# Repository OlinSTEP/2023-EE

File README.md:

# 2023-EE
Firmware and EE documents for 2023 STEP

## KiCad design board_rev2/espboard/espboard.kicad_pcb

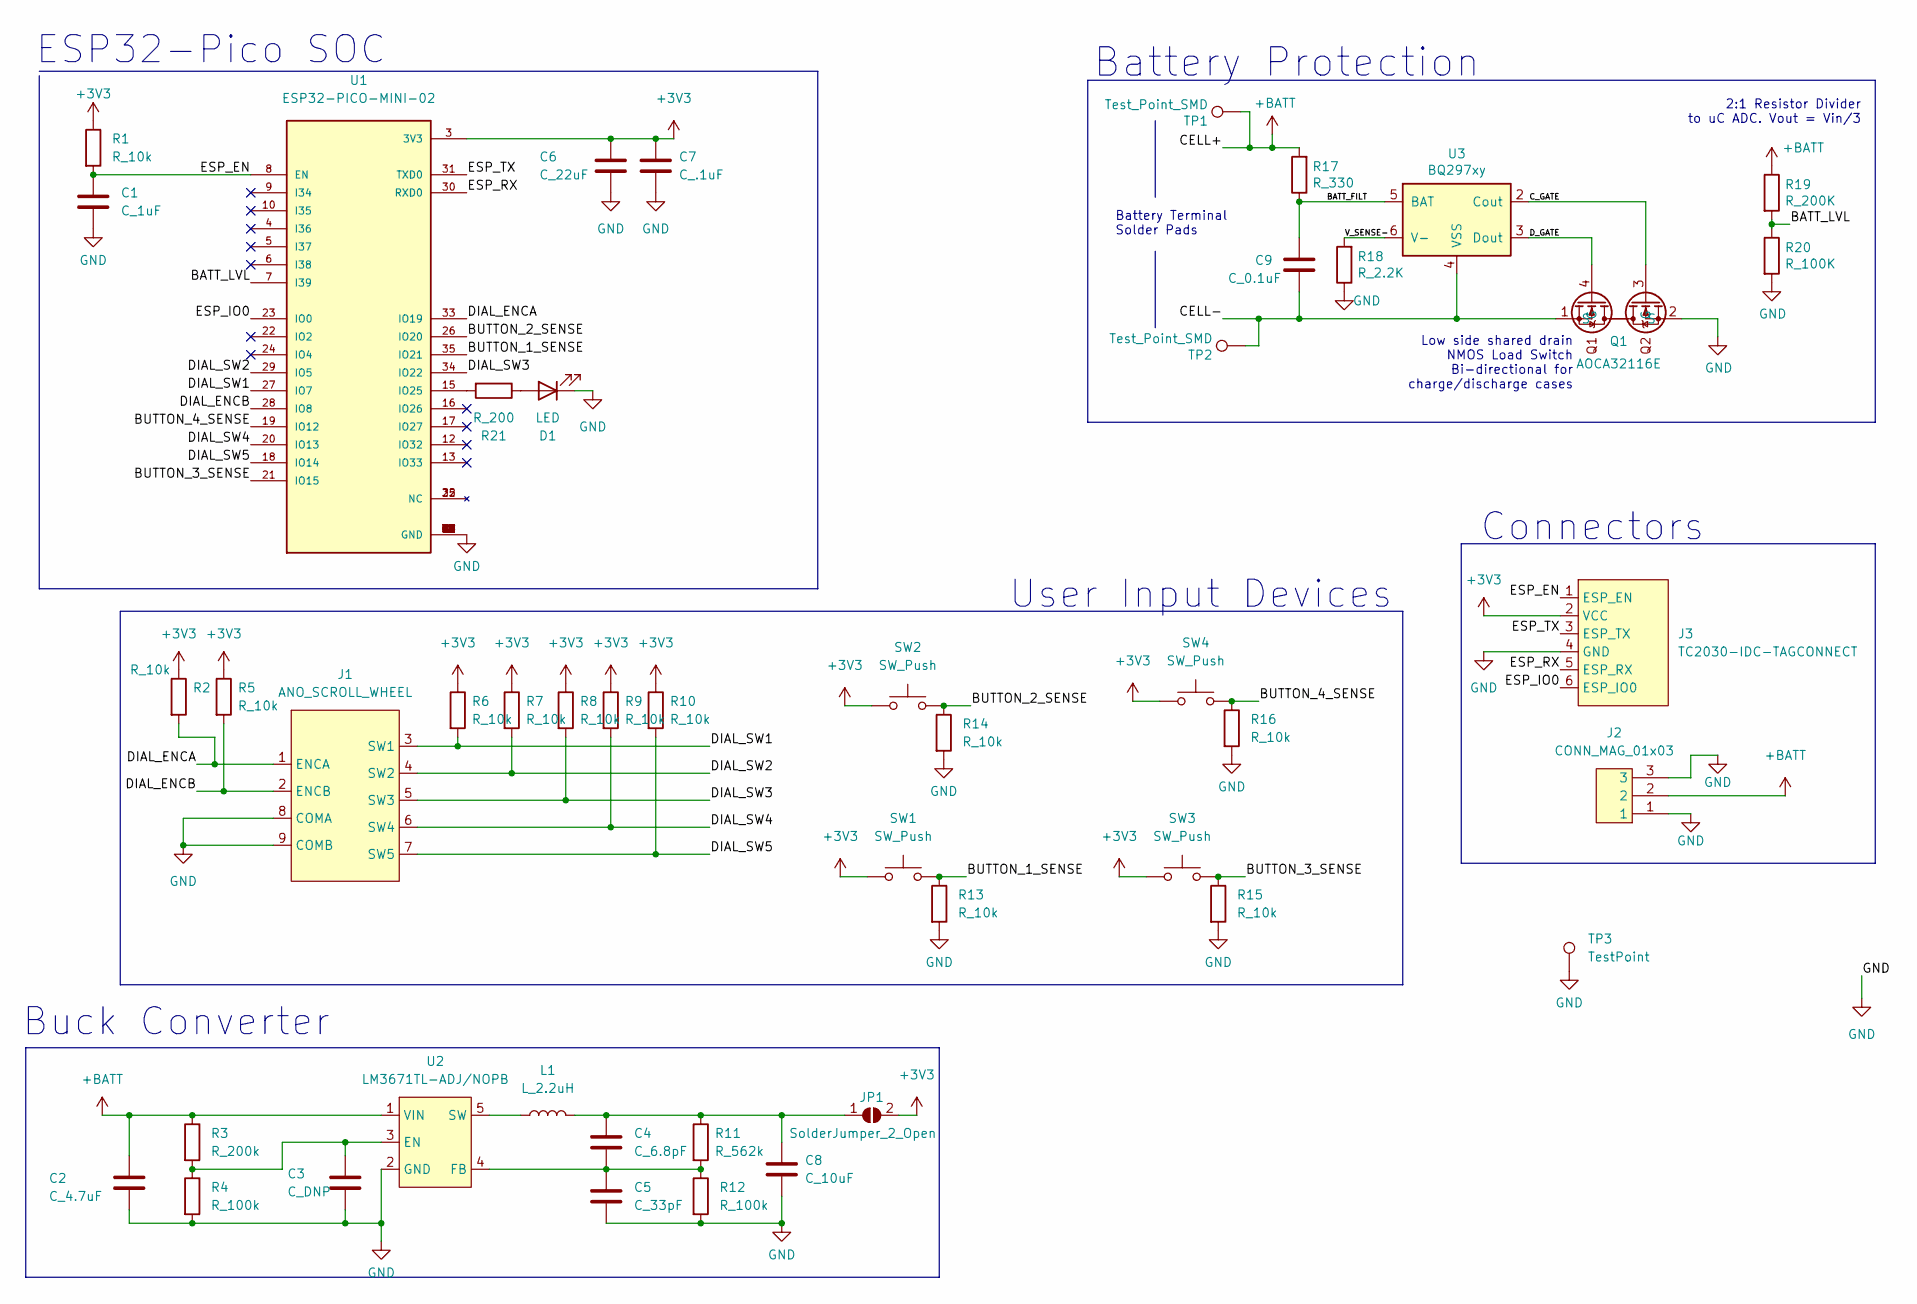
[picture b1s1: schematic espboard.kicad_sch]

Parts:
C1: C_1uF; C_0603_1608Metric
C2: C_4.7uF; C_0603_1608Metric
C3: C_DNP; C_0603_1608Metric
C4: C_6.8pF; C_0603_1608Metric
C5: C_33pF; C_0603_1608Metric
C6: C_22uF; C_0603_1608Metric
C7: C_.1uF; C_0603_1608Metric
C8: C_10uF; C_0603_1608Metric
C9: C_0.1uF; C_0603_1608Metric; MPN 478-3352-1-ND
D1: LED; LED_0805_OEM
J1: ANO_SCROLL_WHEEL
J2: CONN_MAG_01x03; CONN_MAG_1x03
J3: TC2030-IDC-TAGCONNECT; TAG_TC2030-IDC-NL
JP1: SolderJumper_2_Open; SolderJumper-2_P1.3mm_Open_RoundedPad1.0x1.5mm
L1: L_2.2uH; L_0805_2012Metric_Pad1.15x1.40mm_HandSolder
Q1: AOCA32116E
R1, R2, R5, R6, R7, R8, R9, R10, R13, R14, R15, R16: R_10k; R_0603_1608Metric
R3: R_200k; R_0603_1608Metric
R4, R12: R_100k; R_0603_1608Metric
R11: R_562k; R_0603_1608Metric
R17: R_330; R_0603_1608Metric; MPN RMCF0805FT330RCT-ND
R18: R_2.2K; R_0603_1608Metric; MPN RMCF0805FT2K20CT-ND
R19: R_200K; R_0603_1608Metric; MPN P300KDACT-ND
R20: R_100K; R_0603_1608Metric; MPN P100KCCT-ND
R21: R_200; R_0603_1608Metric
SW1, SW2, SW3, SW4: SW_Push; SW_PUSH_6mm
TP1, TP2: Test_Point_SMD; TestPoint_Pad_1.5x1.5mm
TP3: TestPoint; TestPoint_Pad_1.5x1.5mm
U1: ESP32-PICO-MINI-02; MODULE_ESP32-PICO-MINI-02; PARTREV v1.0
U2: LM3671TL-ADJ/NOPB; SOT-23-5
U3: BQ297xy; WSON-6_1.5x1.5mm_P0.5mm

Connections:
+3V3: C6.1, C7.1, J3.2 (VCC), JP1.2 (B), R1.1, R2.1, R5.1, R6.1, R7.1, R8.1, R9.1, R10.1, SW1.1, SW2.1, SW3.1, SW4.1, U1.3 (3V3)
+BATT: C2.1, J2.2, R3.1, R17.2, R19.1, TP1.1, U2.1 (VIN)
/BATT_FILT: C9.1, R17.1, U3.5 (BAT)
/BATT_LVL: R19.2, R20.1, U1.7 (I39)
/BUTTON_1_SENSE: R13.1, SW1.2, U1.35 (IO21)
/BUTTON_2_SENSE: R14.1, SW2.2, U1.26 (IO20)
/BUTTON_3_SENSE: R15.1, SW3.2, U1.21 (IO15)
/BUTTON_4_SENSE: R16.1, SW4.2, U1.19 (IO12)
/CELL-: C9.2, Q1.1 (S), TP2.1, U3.4 (VSS)
/C_GATE: Q1.3 (G), U3.2 (Cout)
/DIAL_ENCA: J1.1 (ENCA), R2.2, U1.33 (IO19)
/DIAL_ENCB: J1.2 (ENCB), R5.2, U1.28 (IO8)
/DIAL_SW1: J1.3 (SW1), R6.2, U1.27 (IO7)
/DIAL_SW2: J1.4 (SW2), R7.2, U1.29 (IO5)
/DIAL_SW3: J1.5 (SW3), R8.2, U1.34 (IO22)
/DIAL_SW4: J1.6 (SW4), R9.2, U1.20 (IO13)
/DIAL_SW5: J1.7 (SW5), R10.2, U1.18 (IO14)
/D_GATE: Q1.4 (G), U3.3 (Dout)
/ESP_EN: C1.1, J3.1 (ESP_EN), R1.2, U1.8 (EN)
/ESP_IO0: J3.6 (ESP_IO0), U1.23 (IO0)
/ESP_RX: J3.5 (ESP_RX), U1.30 (RXD0)
/ESP_TX: J3.3 (ESP_TX), U1.31 (TXD0)
/V_SENSE-: R18.2, U3.6 (V-)
GND: C1.2, C2.2, C3.2, C5.2, C6.2, C7.2, C8.2, D1.1 (K), J1.8 (COMA), J1.9 (COMB), J2.1, J2.3, J3.4 (GND), Q1.2 (S), R4.2, R12.2, R13.2, R14.2, R15.2, R16.2, R18.1, R20.2, TP3.1, U1.1 (GND), U1.2 (GND), U1.11 (GND), U1.14 (GND), U1.36 (GND), U1.37 (GND), U1.38 (GND), U1.39 (GND), U1.40 (GND), U1.41 (GND), U1.42 (GND), U1.43 (GND), U1.44 (GND), U1.45 (GND), U1.46 (GND), U1.47 (GND), U1.48 (GND), U1.49 (GND), U1.50 (GND), U1.51 (GND), U1.52 (GND), U1.53 (GND), U1.54 (GND), U1.55 (GND), U1.56 (GND), U1.57 (GND), U1.58 (GND), U1.59 (GND), U1.60 (GND), U1.61 (GND), U2.2 (GND)
unnamed: C3.1, R3.2, R4.1, U2.3 (EN)
unnamed: C4.1, C8.1, JP1.1 (A), L1.2, R11.1
unnamed: C4.2, C5.1, R11.2, R12.1, U2.4 (FB)
unnamed: D1.2 (A), R21.1
unnamed: L1.1, U2.5 (SW)
unnamed: R21.2, U1.15 (IO25)

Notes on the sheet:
Low side shared drain NMOS Load Switch Bi-directional for charge/discharge cases
Battery Terminal Solder Pads
ESP32-Pico SOC
Battery Protection
Buck Converter
Connectors
User Input Devices
2:1 Resistor Divider to uC ADC. Vout = Vin/3

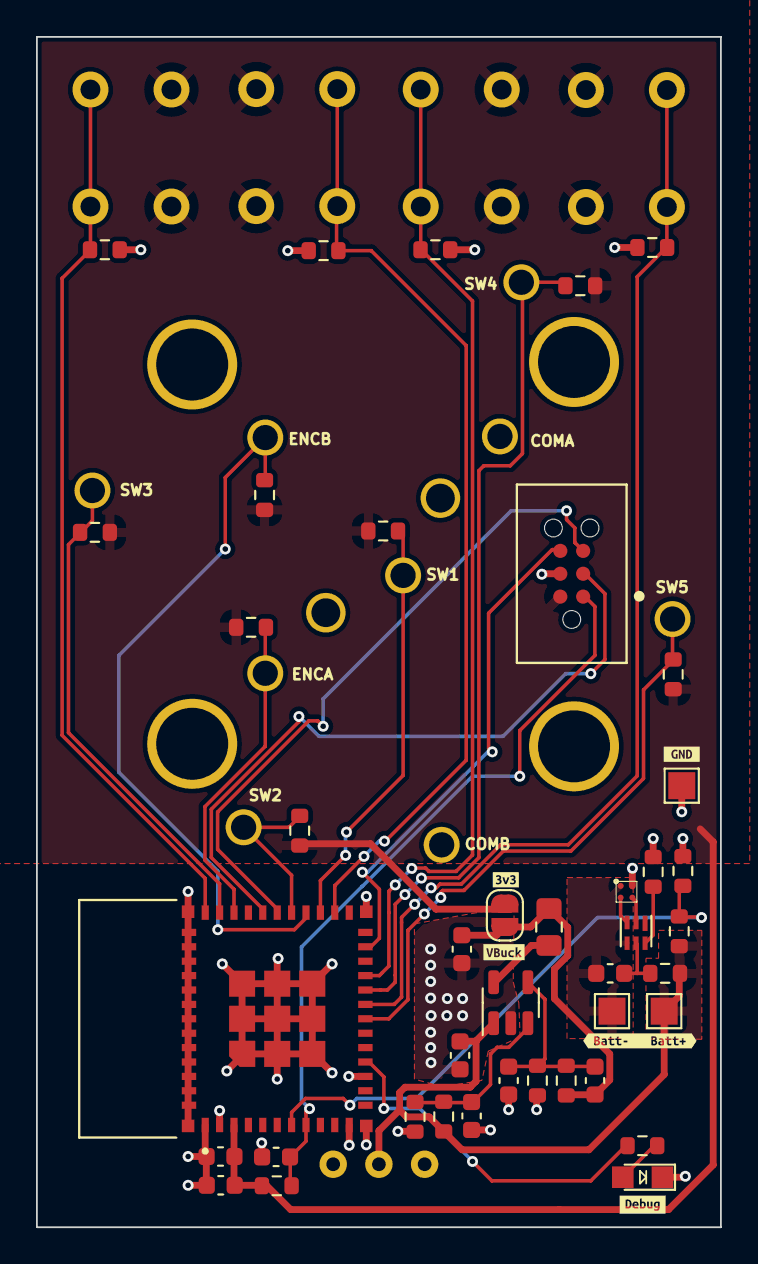
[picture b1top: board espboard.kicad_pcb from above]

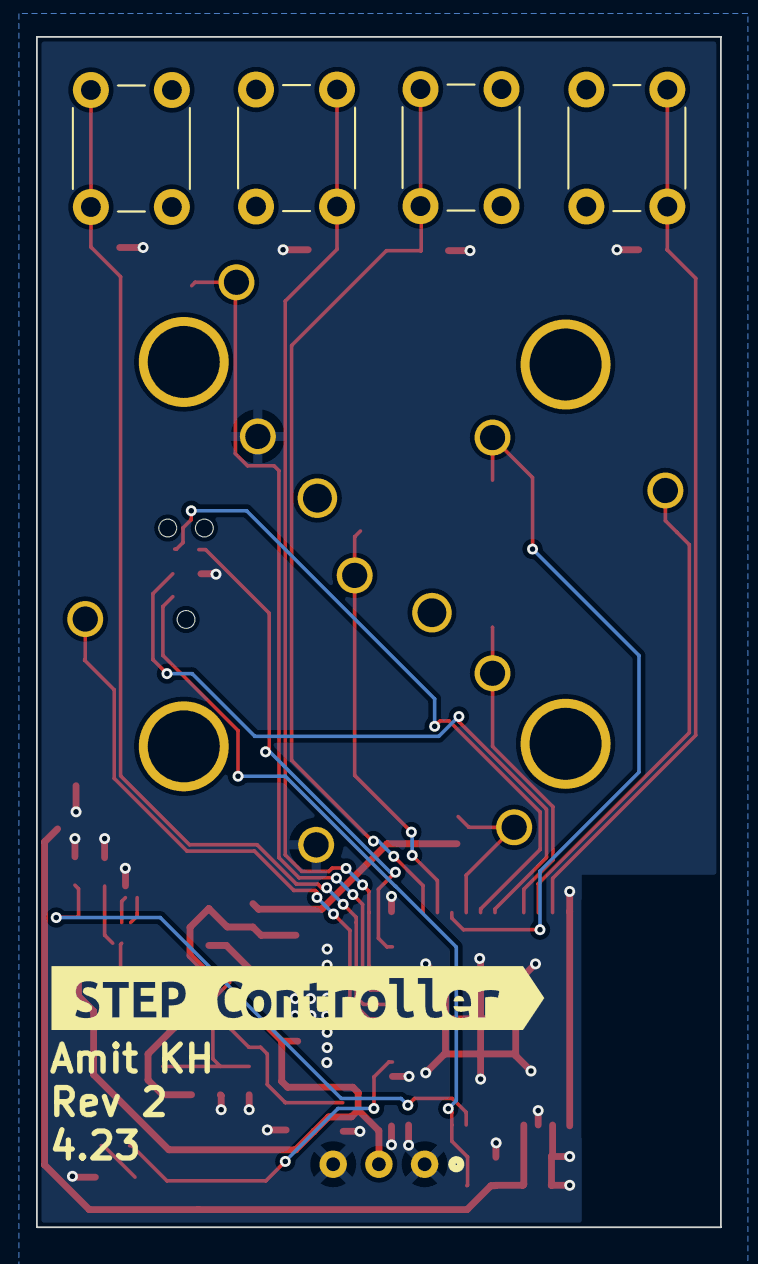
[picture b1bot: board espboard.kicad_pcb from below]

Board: 2 copper layers, 38.0 x 66.1 mm, 53 parts (7 on the bottom side), 30 nets.

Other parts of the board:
kibuzzard-643EED22: G***; kibuzzard-643EED22
kibuzzard-643EF163: G***; kibuzzard-643EF163
kibuzzard-643EF399: G***; kibuzzard-643EF399
kibuzzard-643F0A06: G***; kibuzzard-643F0A06
kibuzzard-643F0B2D: G***; kibuzzard-643F0B2D
kibuzzard-643F0B26: G***; kibuzzard-643F0B26

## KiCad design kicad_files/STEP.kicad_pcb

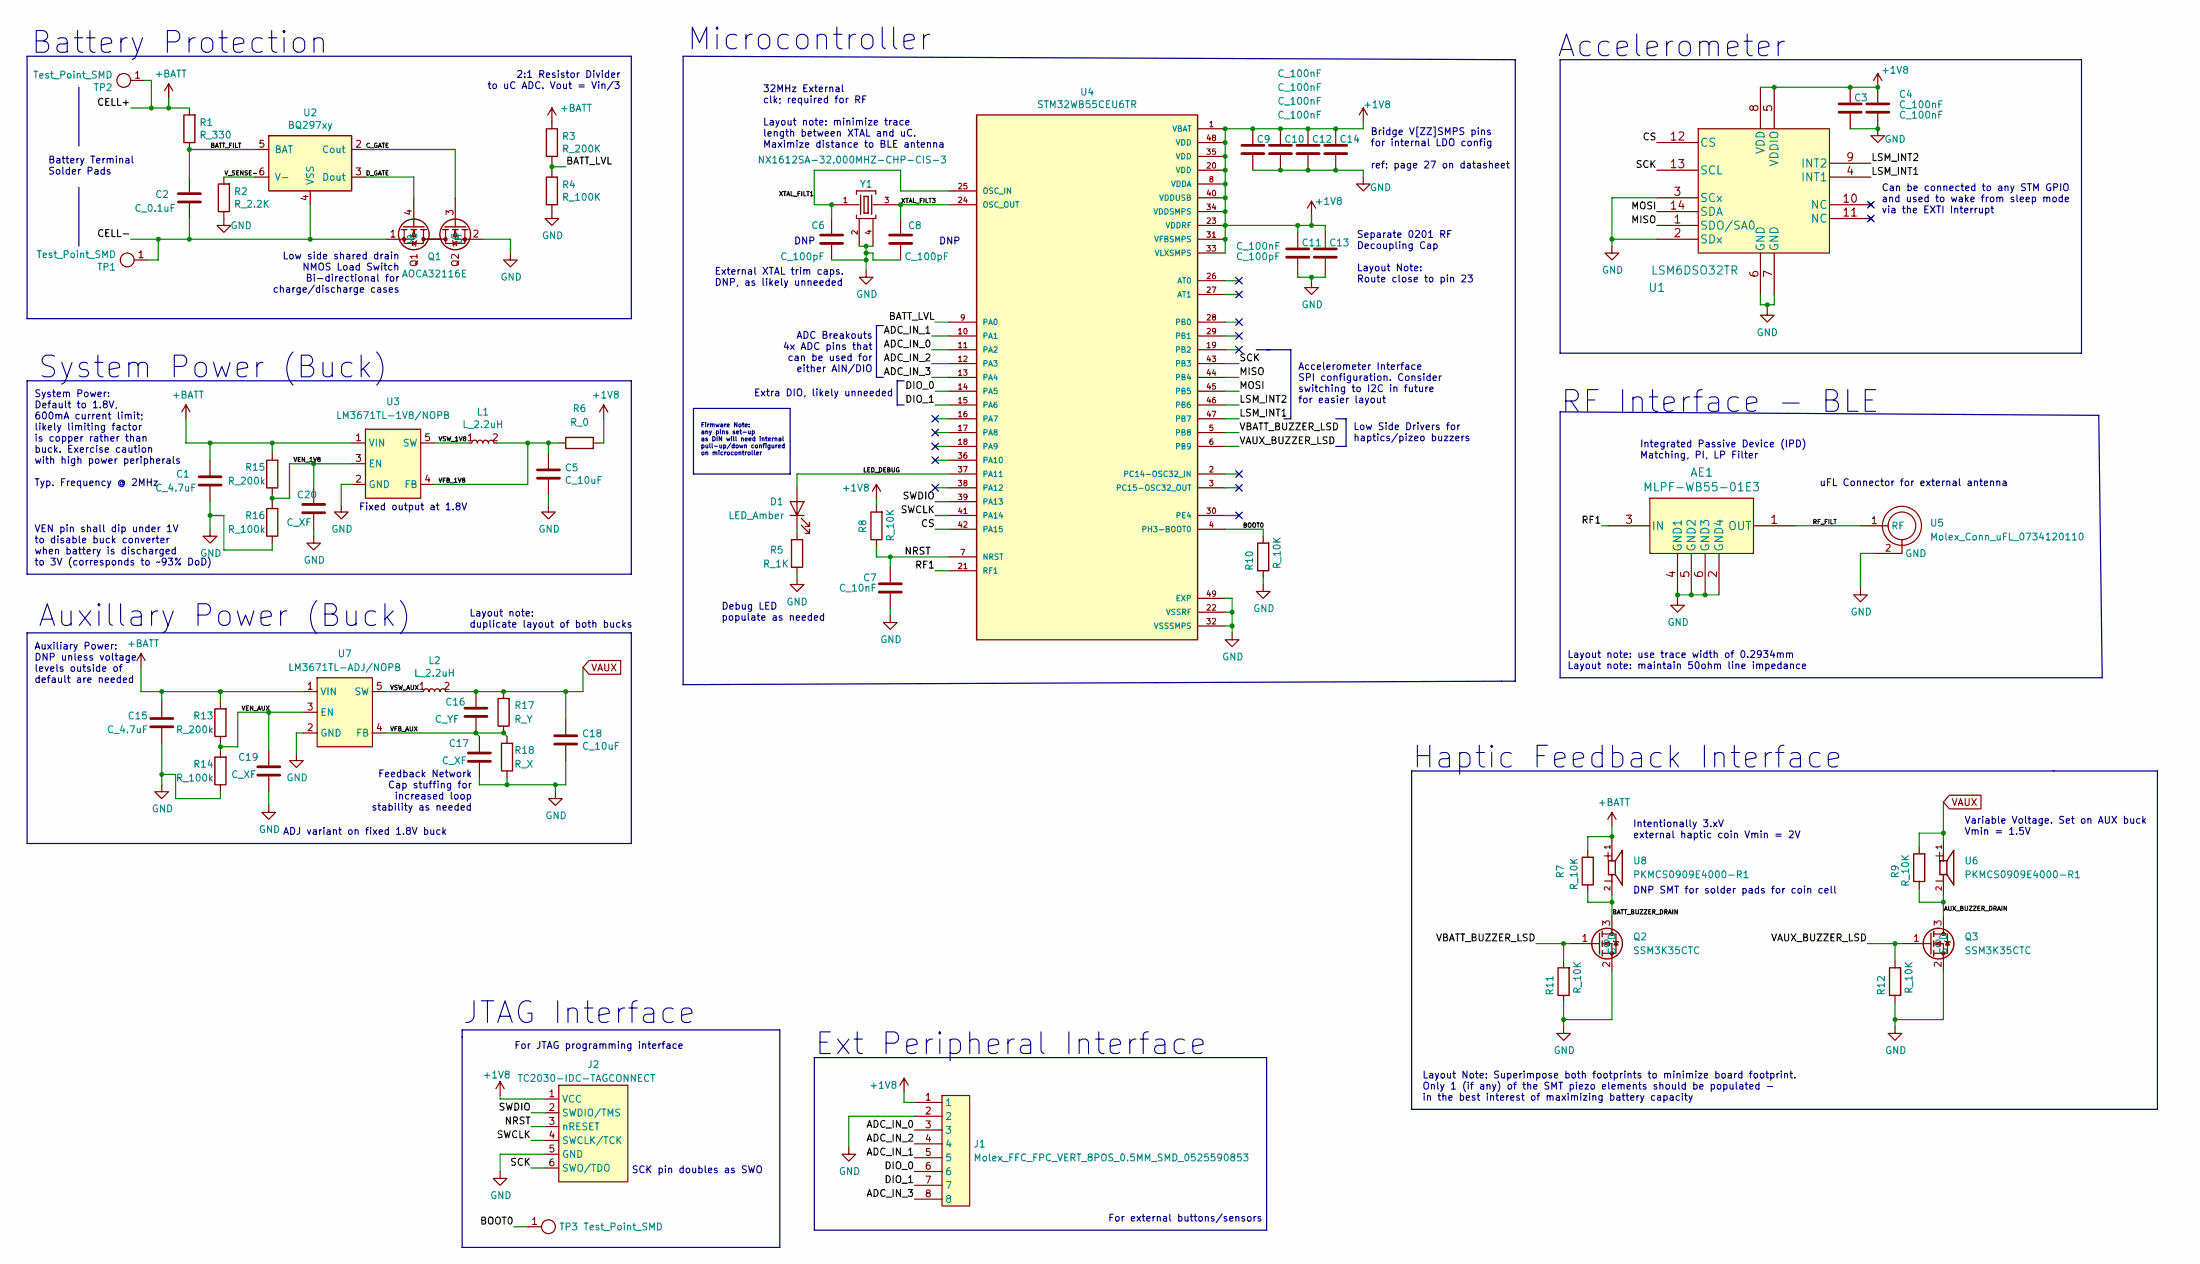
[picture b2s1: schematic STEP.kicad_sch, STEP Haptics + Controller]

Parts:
AE1: MLPF-WB55-01E3
C1, C15: C_4.7uF; C_0402_1005Metric; MPN CL21A475KAQNNNE
C2: C_0.1uF; C_0402_1005Metric; MPN 478-3352-1-ND
C3, C4, C9, C10, C12, C14: C_100nF; C_0402_1005Metric; MPN C0402C104K9RACTU
C5, C18: C_10uF; C_0402_1005Metric; MPN 1276-1052-1-ND
C6, C8, C11: C_100pF; C_0201_0603Metric; MPN 732-7852-1-ND
C7: C_10nF; C_0402_1005Metric; MPN 478-3352-1-ND
C13: C_100nF; C_0201_0603Metric; MPN C0402C104K9RACTU
C16: C_YF; C_0402_1005Metric; MPN C0402C104K9RACTU
C17, C19, C20: C_XF; C_0402_1005Metric; MPN C0402C104K9RACTU
D1: LED_Amber; LED_0402_1005Metric; MPN L71517CT-ND
J1: Molex_FFC_FPC_VERT_8POS_0.5MM_SMD_0525590853; tbf
J2: TC2030-IDC-TAGCONNECT; TAG_TC2030-IDC-NL
L1, L2: L_2.2uH; L_0805_2012Metric_Pad1.05x1.20mm_HandSolder; MPN DFE201612E-2R2M=P2
Q1: AOCA32116E
Q2, Q3: SSM3K35CTC; SOT-883
R1: R_330; R_0402_1005Metric; MPN RMCF0805FT330RCT-ND
R2: R_2.2K; R_0402_1005Metric; MPN RMCF0805FT2K20CT-ND
R3: R_200K; R_0402_1005Metric; MPN P300KDACT-ND
R4: R_100K; R_0402_1005Metric; MPN P100KCCT-ND
R5: R_1K; R_0402_1005Metric; MPN RNCP0805FTD1K00CT-ND
R6: R_0; SolderJumper-2_P1.3mm_Open_TrianglePad1.0x1.5mm; MPN P0.0GCT-ND
R7, R9, R10, R11, R12: R_10K; R_0402_1005Metric; MPN P300KDACT-ND
R8: R_10K; R_0402_1005Metric; MPN RNCP0805FTD1K00CT-ND
R13, R15: R_200k; R_0402_1005Metric; MPN RMCF0805FT330RCT-ND
R14, R16: R_100k; R_0402_1005Metric; MPN RMCF0805FT330RCT-ND
R17: R_Y; R_0402_1005Metric; MPN RMCF0805FT330RCT-ND
R18: R_X; R_0402_1005Metric; MPN RMCF0805FT330RCT-ND
TP1, TP2: Test_Point_SMD; TestPoint_Pad_1.5x1.5mm
TP3: Test_Point_SMD; TestPoint_Pad_D1.0mm
U1: LSM6DSO32TR
U2: BQ297xy; WSON-6_1.5x1.5mm_P0.5mm
U3: LM3671TL-1V8/NOPB; SOT-23-5
U4: STM32WB55CEU6TR; QFN50P700X700X60-49N; PARTREV 5
U5: Molex_Conn_uFL_0734120110; U.FL_Molex_MCRF_73412-0110_Vertical
U6, U8: PKMCS0909E4000-R1; SPKR_PKMCS0909E4000-R1
U7: LM3671TL-ADJ/NOPB; SOT-23-5
Y1: NX1612SA-32.000MHZ-CHP-CIS-3; OSCSC105P160X120X35-4N

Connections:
+1V8: C3.1, C4.1, C9.1, C10.1, C11.1, C12.1, C13.1, C14.1, J1.1, J2.1 (VCC), R6.2, R8.2, U1.5 (VDDIO), U1.8 (VDD), U4.1 (VBAT), U4.8 (VDDA), U4.20 (VDD), U4.23 (VDDRF), U4.31 (VFBSMPS), U4.33 (VLXSMPS), U4.34 (VDDSMPS), U4.35 (VDD), U4.40 (VDDUSB), U4.48 (VDD)
+BATT: C1.1, C15.1, R1.2, R3.1, R7.2, R13.2, R15.2, TP2.1, U3.1 (VIN), U7.1 (VIN), U8.1
/ADC_IN_0: J1.3, U4.11 (PA2)
/ADC_IN_1: J1.5, U4.10 (PA1)
/ADC_IN_2: J1.4, U4.12 (PA3)
/ADC_IN_3: J1.8, U4.13 (PA4)
/AUX_BUZZER_DRAIN: Q3.3 (D), R9.1, U6.2
/BATT_BUZZER_DRAIN: Q2.3 (D), R7.1, U8.2
/BATT_FILT: C2.1, R1.1, U2.5 (BAT)
/BATT_LVL: R3.2, R4.1, U4.9 (PA0)
/BOOT0: R10.2, TP3.1, U4.4 (PH3-BOOT0)
/CELL-: C2.2, Q1.1 (S), TP1.1, U2.4 (VSS)
/CS: U1.12 (CS), U4.42 (PA15)
/C_GATE: Q1.3 (G), U2.2 (Cout)
/DIO_0: J1.6, U4.14 (PA5)
/DIO_1: J1.7, U4.15 (PA6)
/D_GATE: Q1.4 (G), U2.3 (Dout)
/LED_DEBUG: D1.2 (A), U4.37 (PA11)
/LSM_INT1: U1.4 (INT1), U4.47 (PB7)
/LSM_INT2: U1.9 (INT2), U4.46 (PB6)
/MISO: U1.1 (SDO/SA0), U4.44 (PB4)
/MOSI: U1.14 (SDA), U4.45 (PB5)
/NRST: C7.1, J2.3 (nRESET), R8.1, U4.7 (NRST)
/RF1: AE1.3 (IN), U4.21 (RF1)
/RF_FILT: AE1.1 (OUT), U5.1 (RF)
/SCK: J2.6 (SWO/TDO), U1.13 (SCL), U4.43 (PB3)
/SWCLK: J2.4 (SWCLK/TCK), U4.41 (PA14)
/SWDIO: J2.2 (SWDIO/TMS), U4.39 (PA13)
/VAUX_BUZZER_LSD: Q3.1 (G), R12.2, U4.6 (PB9)
/VBATT_BUZZER_LSD: Q2.1 (G), R11.2, U4.5 (PB8)
/VEN_1V8: C20.1, R15.1, R16.2, U3.3 (EN)
/VEN_AUX: C19.1, R13.1, R14.2, U7.3 (EN)
/VFB_1V8: C5.1, L1.2, R6.1, U3.4 (FB)
/VFB_AUX: C16.2, C17.1, R17.1, R18.2, U7.4 (FB)
/VSW_1V8: L1.1, U3.5 (SW)
/VSW_AUX: L2.1, U7.5 (SW)
/V_SENSE-: R2.2, U2.6 (V-)
/XTAL_FILT1: C6.1, U4.25 (OSC_IN), Y1.1
/XTAL_FILT3: C8.1, U4.24 (OSC_OUT), Y1.3
GND: AE1.2 (GND4), AE1.4 (GND1), AE1.5 (GND2), AE1.6 (GND3), C1.2, C3.2, C4.2, C5.2, C6.2, C7.2, C8.2, C9.2, C10.2, C11.2, C12.2, C13.2, C14.2, C15.2, C17.2, C18.2, C19.2, C20.2, J1.2, J2.5 (GND), Q1.2 (S), Q2.2 (S), Q3.2 (S), R2.1, R4.2, R5.2, R10.1, R11.1, R12.1, R14.1, R16.1, R18.1, U1.2 (SDx), U1.3 (SCx), U1.6 (GND), U1.7 (GND), U3.2 (GND), U4.22 (VSSRF), U4.32 (VSSSMPS), U4.49 (EXP), U5.2 (GND), U7.2 (GND), Y1.2, Y1.4
unnamed: D1.1 (K), R5.1
VAUX: C16.1, C18.1, L2.2, R9.2, R17.2, U6.1

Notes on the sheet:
Low Side Drivers for haptics/pizeo buzzers
System Power (Buck)
DNP
Variable Voltage. Set on AUX buck Vmin = 1.5V
Layout note: use trace width of 0.2934mm Layout note: maintain 50ohm line impedance
Layout note: duplicate layout of both bucks
Bridge V[ZZ]SMPS pins for internal LDO config ref: page 27 on datasheet
Auxiliary Power: DNP unless voltage levels outside of default are needed
For external buttons/sensors
Can be connected to any STM GPIO and used to wake from sleep mode via the EXTI Interrupt
ADC Breakouts 4x ADC pins that can be used for either AIN/DIO
Intentionally 3.xV external haptic coin Vmin = 2V
Extra DIO, likely unneeded
ADJ variant on fixed 1.8V buck
Low side shared drain NMOS Load Switch Bi-directional for charge/discharge cases
Accelerometer Interface SPI configuration. Consider switching to I2C in future for easier layout
JTAG Interface
Ext Peripheral Interface
RF Interface - BLE
DNP SMT for solder pads for coin cell
Feedback Network Cap stuffing for increased loop stability as needed
SCK pin doubles as SWO
Auxillary Power (Buck)
Integrated Passive Device (IPD) Matching, PI, LP Filter
External XTAL trim caps. DNP, as likely unneeded
Fixed output at 1.8V
Layout Note: Superimpose both footprints to minimize board footprint. Only 1 (if any) of the SMT piezo elements should be populated - in the best interest of maximizing battery capacity
VEN pin shall dip under 1V to disable buck converter when battery is discharged to 3V (corresponds to ~93% DoD)
32MHz External clk; required for RF Layout note: minimize trace length between XTAL and uC. Maximize distance to BLE antenna
Haptic Feedback Interface
For JTAG programming interface
Accelerometer
Debug LED populate as needed
uFL Connector for external antenna
Separate 0201 RF Decoupling Cap Layout Note: Route close to pin 23
Firmware Note: any pins set-up as DIN will need internal pull-up/down configured on microcontroller
2:1 Resistor Divider to uC ADC. Vout = Vin/3
Battery Terminal Solder Pads
Battery Protection
Microcontroller

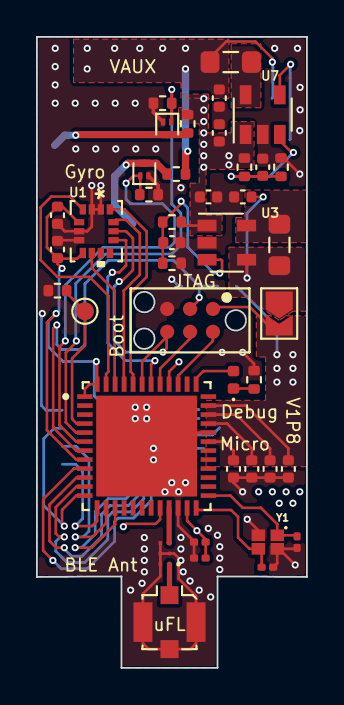
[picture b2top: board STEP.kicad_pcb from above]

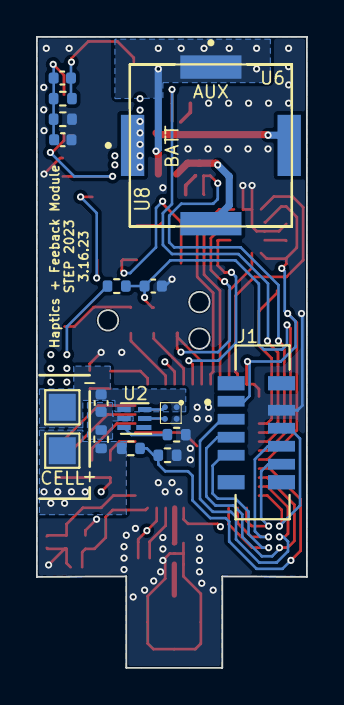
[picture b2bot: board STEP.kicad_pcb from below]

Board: 4 copper layers, 15.0 x 35.1 mm, 59 parts (18 on the bottom side), 42 nets.

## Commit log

2023-03-03 Added kicad files
2023-03-06 Added previous modules to schematic and edited MCU pinouts for 2023 project
2023-03-07 new buck, fixed mc pinout, improvements from v0 ring, haptics, connectors and ADCs
2023-03-07 updated pinout, buck, v0 changes, added library parts
2023-03-08 added aux buck, fixed haptic circuit nets
2023-03-11 finished v0.9 schematic and layout, annotated for review
2023-03-11 exported pdf of schematic for review
2023-03-11 adjusted single via
2023-03-17 post design review feedback, switching to external antenna for prototyping
2023-03-30 add blinky
2023-04-11 add rev 2 board schematic
2023-04-18 update parts libs
2023-04-18 layout rev done
2023-04-18 ready for review

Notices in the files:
parts and their libraries:
Copyright 2021 Accelerated Designs. All rights reserved.
